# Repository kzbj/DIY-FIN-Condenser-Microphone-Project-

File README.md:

# DIY FIN Condenser Microphone

A DIY studio condenser microphone based on the **FIN circuit**: a transformerless, phantom-powered (48V) design with a JFET input stage and an XLR output.

This repository contains my schematic and PCB in two versions (KiCad and Altium Designer), the Bill of Materials (BOM), sourcing notes (including local options in Prague), and build progress notes.

---

## Project Status

**Current status:** in progress

- [x] Schematic redrawn in KiCad
- [x] BOM compiled
- [x] PCB laid out in KiCad (DRC clean)
- [x] Schematic and PCB redrawn in Altium Designer — rev. 2 (DRC clean, 0 violations)
- [ ] Verify open questions against the original schematic (see below)
- [ ] Check custom footprints against real parts (1:1 printout)
- [x] Order PCB: 5 boards from JLCPCB (Altium rev. 2, Ø54 mm), November 2026, 14.62 EUR
- [ ] Buy a replacement capsule
- [ ] Source special components (3GΩ resistors, JFET, inductors)
- [ ] Assemble and test
- [ ] Design an enclosure

Not all components are available off the shelf in local stores (e.g. 3GΩ resistors, the JFET, the inductors), so I document substitutes and sourcing workarounds as I go.

---

## Background

The project is based on a YouTube Short by **[Alexey Kostrykin](https://www.youtube.com/@AlexeyKostrykin/shorts)**, *["Микрофон по схеме FIN"](https://www.youtube.com/shorts/0v5QWER9Aq8)*, where the voiceover is recorded with the microphone itself.

The author published a **[Google Drive folder](https://drive.google.com/drive/folders/1b-6JGVSPCHNgb5s343AQEgBrW2yjJV4H?usp=drive_link)** with schematics, PCB layouts, test recordings and assembly notes. This repository documents my own build: redrawing the circuit in KiCad and Altium Designer, designing my own PCB, sourcing parts and substituting obsolete components.

---

## Schematic

## PCB

| Top | Bare board | Bottom |
|---|---|---|
|  |  |  |

My own PCB design, made from scratch rather than copied from the original layout, because I use a different capsule. Designed in KiCad 10: round board, all components on one side, single-layer (F.Cu) routing.

- **Capsule and XLR are wired, not board-mounted:** both connect to solder-wire pads on the board (capsule: 2 pads, XLR: 3 pads).
- **Ground ring** around the board edge (net `Earth`).
- **Two solder pads on the ring (J2, J3)** for shielded/braided wire connecting PCB ground to the metal body.
- **Layout zones:**
  - capsule and JFET gate node (MK1, R13, C9, R12, Q3, R10, R11), with short traces and no copper pour nearby because of the gigaohm impedance;
  - amplifier / output stage (Q1, Q2, R6–R9, C7, C8, C10, D1);
  - RF filter next to the XLR pads (R3, R4, R5, C3, C6, L1, L2).

---

## Altium Designer version (rev. 2)

The `altium/` folder contains a second, revised version of the project, redrawn from scratch in **Altium Designer** (schematic and PCB). I made it to learn Altium and to correct and improve the KiCad design. Designators are the same as in the KiCad version.

### Schematic (Altium)

Full-resolution PDF: [schematics/fin-microphone-altium.pdf](schematics/fin-microphone-altium.pdf)

### PCB (Altium)

| 2D layout | 3D top | 3D bottom (GND pour) |
|---|---|---|
|  |  |  |

### Changes compared to the KiCad version

- **Board area changed:** round board, Ø54 mm (the KiCad version is Ø56 mm).
- **Components selected against real parts:** every part was checked against an actual manufacturer part number (see the table below), not a generic footprint.
- **Ground pour inside the board:** a GND copper pour on the bottom layer, in addition to the ground ring around the edge.
- **Via added** for the ground connection between layers.
- **No copper around the gigaohm node:** the pour is cut out around the capsule and JFET gate area (J1, R12, R13, C9, Q3 gate) to avoid leakage and noise.
- **Custom symbols and footprints:** several parts had no ready-made models, so I drew my own:
  - 3GΩ resistor (radial SM102 body);
  - capsule (2 wire pads), XLR (3 wire pads), braid/ground (1 pad).
- **Component models from SnapMagic:** symbols and footprints for the transistors, JFET, inductors and capacitors were found on SnapMagic and imported into Altium.

### Parts used in the Altium version

| Ref | Part | Notes |
|---|---|---|
| Q3 | MMBF5457 | JFET, SOT-23 |
| Q1 | BC857B | PNP, SOT-23 |
| Q2 | BC847C | NPN, SOT-23 |
| L1, L2 | BRL3225T1R0M | 1.0µH, 1210 SMD |
| C3, C6 | FG28C0G2A681JNT00 | 680pF C0G, 100V, 5mm pitch |
| R12, R13 | 3GΩ, SM102-type body | custom footprint |

### Files

- `altium/fin-microphone.PrjPcb`: project
- `altium/fin-microphone.SchDoc`: schematic
- `altium/fin-microphone.PcbDoc`: PCB
- `altium/fin-microphone.SchLib`, `altium/fin-microphone.PcbLib`: custom symbols and footprints
- `altium/libs/`: imported component libraries

---

## Bill of Materials (BOM)

### 1. Capsule

The original 26mm capsule (ordered from China) never arrived after about three months, so I am switching to a **34mm capsule**.

- **Planned:** K47-type, single backplate, 2 terminals (sold as "RK-47" / "K47 capsule"), about 20–30 EUR.
- **Why K47 rather than K67:** K67-type capsules have a high-frequency lift that is meant to be corrected by the U67/U87 circuit. This circuit has no such correction, so a K67 would sound bright. A dual-diaphragm K67 still works if only the front diaphragm is connected.
- **Status:** not purchased yet.

### 2. Standard Components (GM Electronic, Prague)

| # | Component | Value / Part | Qty | Notes |
|---|---|---|---|---|
| 1 | Resistor | 47Ω | 2x | Metal film 0.6W 1%, THT |
| 2 | Resistor | 47kΩ | 2x | Metal film 0.6W 1%, THT |
| 3 | Resistor | 2MΩ | 1x | Metal film 0.6W 1%, THT |
| 4 | Resistor | 1MΩ | 1x | Metal film 0.6W 1%, THT |
| 5 | Resistor | 6R (see open questions) | 1x | Metal film 0.6W 1%, THT |
| 6 | Resistor | 12kΩ | 1x | Metal film 0.6W 1%, THT |
| 7 | Resistor | 5.6kΩ | 1x | Metal film 0.6W 1%, THT |
| 8 | Capacitor | 47µF | 2x | Electrolytic, 25–50V |
| 9 | Capacitor | 470µF | 1x | Electrolytic, 25–50V |
| 10 | Capacitor | 680pF | 2x | Film / ceramic, 5mm pitch |
| 11 | Capacitor | 1000pF (1nF) | 1x | Film / ceramic, 5mm pitch |
| 12 | Transistor | BC857B | 1x | PNP, SOT-23 |
| 13 | Transistor | BC847C | 1x | NPN, SOT-23 |
| 14 | Diode | 1N4148 | 1x | DO-35 THT (PCB uses the THT footprint; LL4148 is the SMD equivalent) |
| 15 | Connector | XLR male, 3-pin | 1x | Panel mount, wired to the PCB |

### 3. Special Components (Mouser / TME)

| Component | Value / Part | Qty | Notes |
|---|---|---|---|
| Resistor | 3GΩ | 2x | Capsule polarization and gate bias; rare value, alternatives: 3x 1GΩ in series or the nearest available value (exact value is not critical) |
| Inductor | 0.7µH | 2x | SMD, RF filter |
| JFET | MMBF5457 | 1x | SOT-23, soldered directly to the PCB; SMD replacement for the obsolete 2N5457 (TO-92) |

---

## Cost

| Item | Source | Price |
|---|---|---|
| PCB, 5 pcs (Ø54 mm, Altium rev. 2) | JLCPCB | 14.62 EUR total (≈ 2.92 EUR per board) |
| Standard components | GM Electronic | to be added |
| Special components (3GΩ resistors, JFET, inductors) | Mouser / TME | to be added |
| Capsule | eBay / AliExpress | to be added |

---

## Open Questions

To verify against the original schematic before ordering the PCB:

1. **R3 value:** it reads as 6R (6Ω) on my copy, but it may be 6.8kΩ. The original photo is ambiguous.
2. **R3 / R4 connection** at XLR pin 2: pin 3 has no matching resistor next to its 680pF capacitor, so this needs checking.
3. **D1 polarity:** in my schematic, the D1 anode is connected to the supply rail (C10 +). Check the direction against the original.

---

## Sourcing Notes (Prague, Czech Republic)

- **GM Electronic** (Křižíkova 147/77, Prague 8): local pick-up for standard passives, the XLR connector, BC transistors and the diode.
- **Mouser / TME:** online orders for the 3GΩ resistors, MMBF5457 and inductors.
- **eBay / AliExpress:** capsule. After the first order was lost, I plan to order from high-rated sellers with tracking, possibly from two sellers in parallel.

---

## Repository Structure

- `/kicad`: my KiCad project (schematic and PCB)
- `/altium`: my Altium Designer project, rev. 2 (schematic, PCB, custom libraries)
- `/schematics`: schematic exported from KiCad (SVG/PDF); the original FIN files are in the author's Google Drive (link above)
- `/photos`: build progress and photos of the finished microphone
- `/docs`: datasheets and notes on workarounds

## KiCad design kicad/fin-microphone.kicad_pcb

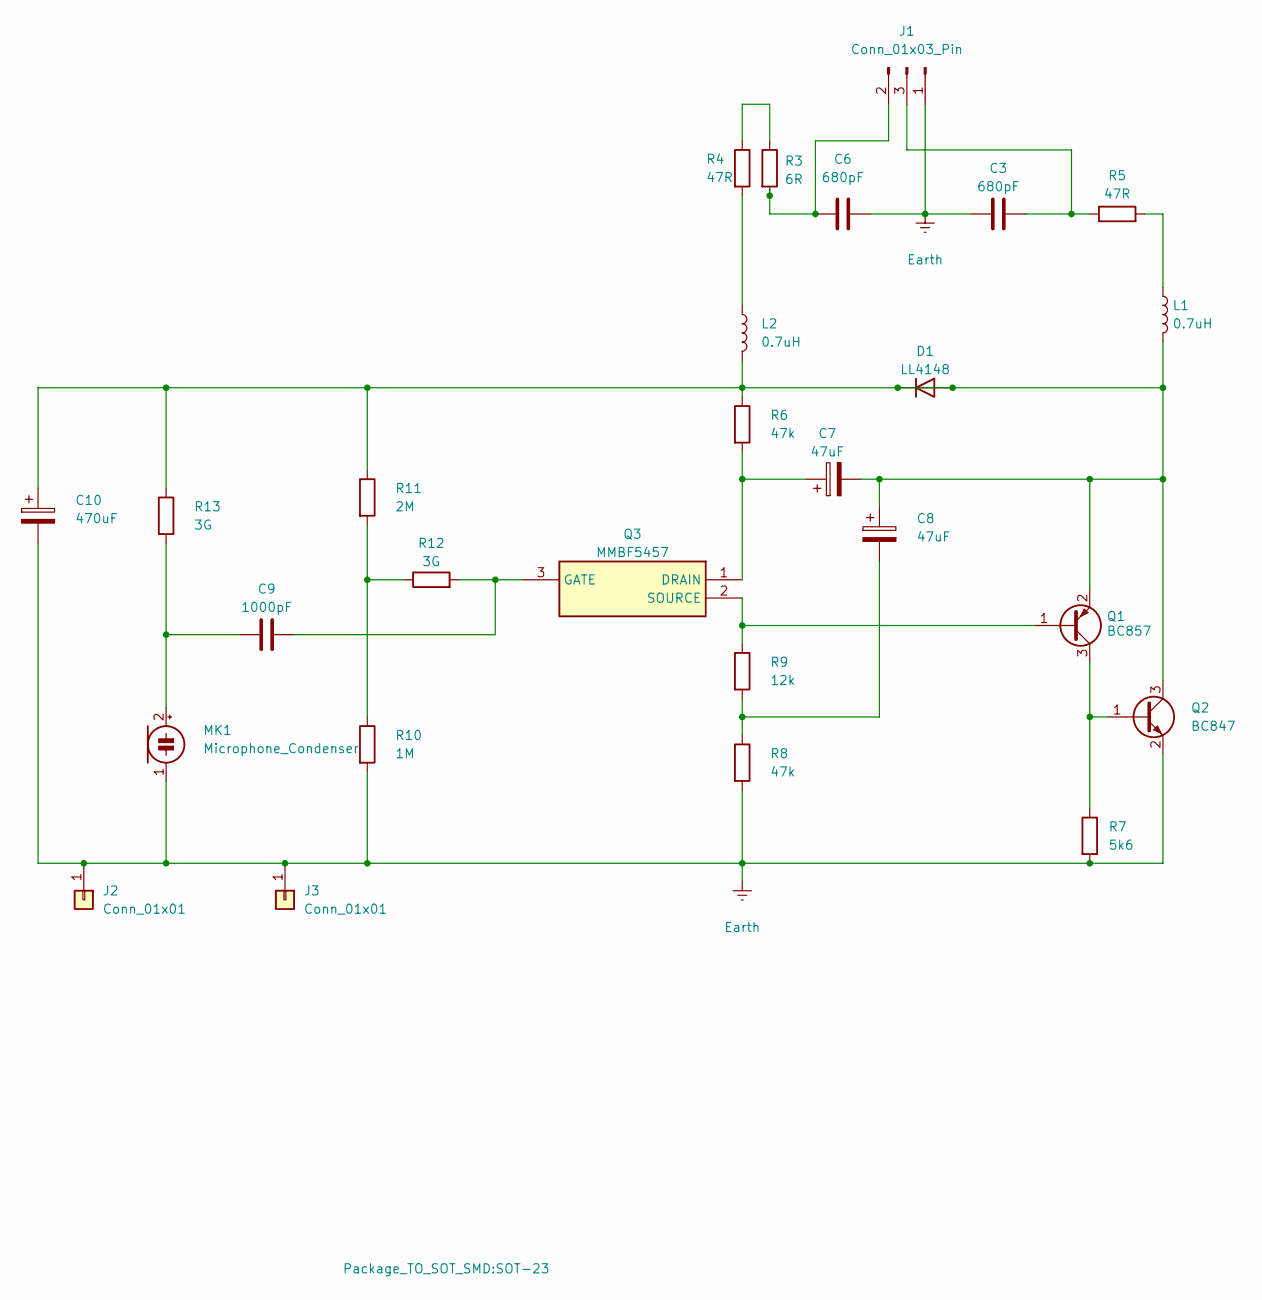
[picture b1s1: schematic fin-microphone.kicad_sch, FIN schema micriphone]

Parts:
C3, C6: 680pF; C_Disc_D5.0mm_W2.5mm_P5.00mm
C7, C8: 47uF; CP_Radial_D5.0mm_P2.50mm
C9: 1000pF; C_Disc_D5.0mm_W2.5mm_P5.00mm
C10: 470uF; CP_Radial_D10.0mm_P5.00mm
D1: LL4148; D_DO-35_SOD27_P7.62mm_Horizontal
J1: Conn_01x03_Pin; PinHeader_1x03_P2.54mm_Vertical
J2, J3: Conn_01x01; SolderWire-1sqmm_1x01_D1.4mm_OD2.7mm
L1, L2: 0.7uH; L_1210_3225Metric_Pad1.42x2.65mm_HandSolder
MK1: Microphone_Condenser; SolderWire-0.127sqmm_1x02_P3.7mm_D0.48mm_OD1mm
Q1: BC857; SOT-23
Q2: BC847; SOT-23
Q3: MMBF5457; SOT-23; Mouser Part Number 512-MMBF5457
R3: 6R; R_Axial_DIN0207_L6.3mm_D2.5mm_P7.62mm_Horizontal
R4, R5: 47R; R_Axial_DIN0207_L6.3mm_D2.5mm_P7.62mm_Horizontal
R6, R8: 47k; R_Axial_DIN0207_L6.3mm_D2.5mm_P7.62mm_Horizontal
R7: 5k6; R_Axial_DIN0207_L6.3mm_D2.5mm_P7.62mm_Horizontal
R9: 12k; R_Axial_DIN0207_L6.3mm_D2.5mm_P7.62mm_Horizontal
R10: 1M; R_Axial_DIN0207_L6.3mm_D2.5mm_P7.62mm_Horizontal
R11: 2M; R_Axial_DIN0207_L6.3mm_D2.5mm_P7.62mm_Horizontal
R12, R13: 3G; R_Box_L13.0mm_W4.0mm_P9.00mm

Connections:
Earth: C3.2, C6.2, C10.2, J1.1, J2.1 (Pin_1_1), J3.1 (Pin_1_1), MK1.1 (-), Q2.2 (E), R7.2, R8.2, R10.2
unnamed: C8.2, R8.1, R9.2
unnamed: C7.2, C8.1, C10.1, D1.1 (K), D1.2 (A), L1.2, L2.2, Q1.2 (E), Q2.3 (C), R6.1, R11.1, R13.1
unnamed: C6.1, J1.2, R3.2
unnamed: C3.1, J1.3, R5.1
unnamed: L1.1, R5.2
unnamed: L2.1, R4.2
unnamed: C9.1, MK1.2 (+), R13.2
unnamed: Q1.1 (B), Q3.2 (SOURCE), R9.1
unnamed: Q1.3 (C), Q2.1 (B), R7.1
unnamed: C7.1, Q3.1 (DRAIN), R6.2
unnamed: C9.2, Q3.3 (GATE), R12.2
unnamed: R3.1, R4.1
unnamed: R10.1, R11.2, R12.1

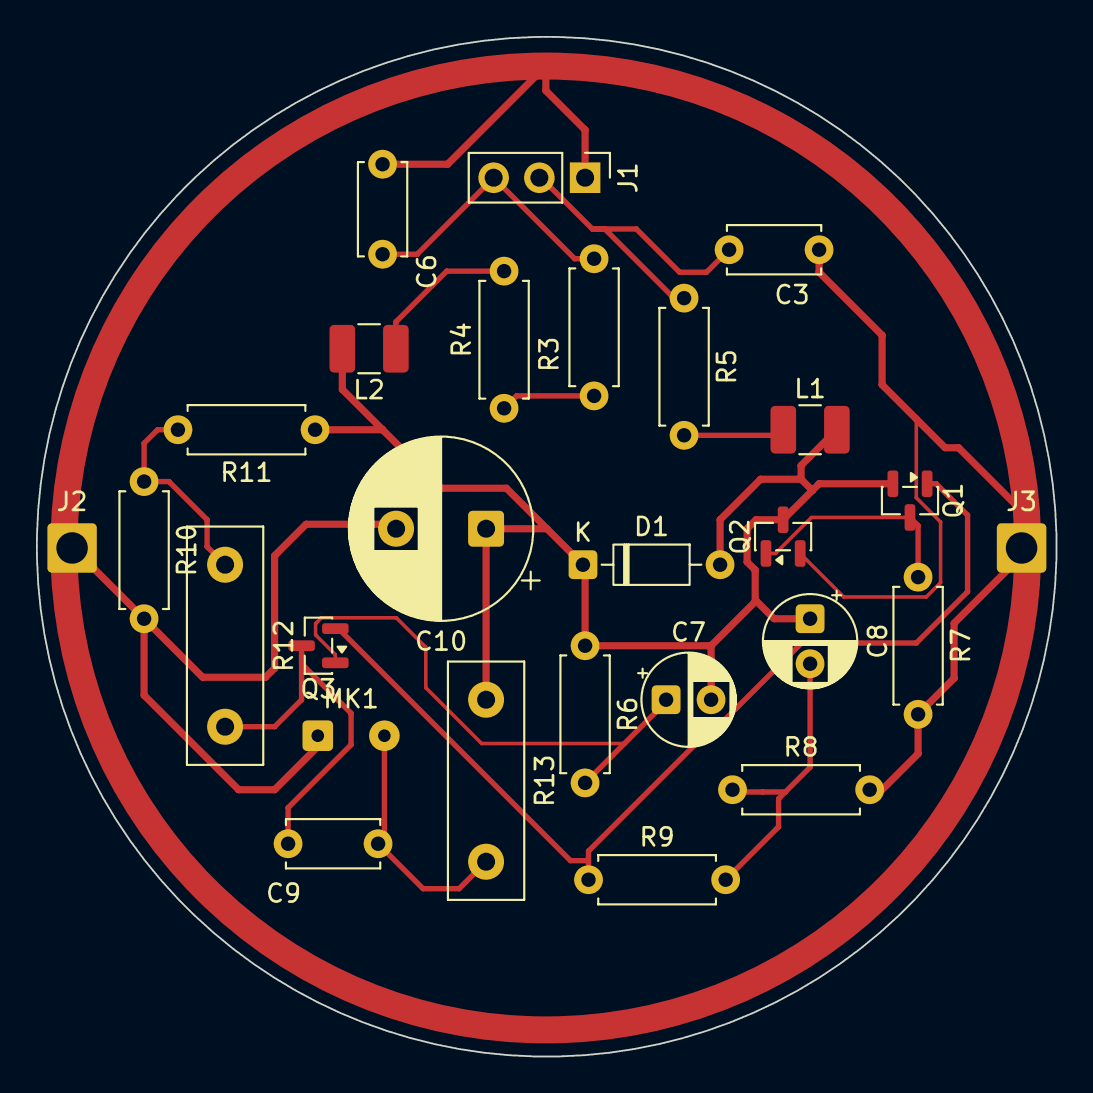
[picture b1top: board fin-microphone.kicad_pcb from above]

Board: 2 copper layers, 56.6 x 56.6 mm, 27 parts (0 on the bottom side), 14 nets.
